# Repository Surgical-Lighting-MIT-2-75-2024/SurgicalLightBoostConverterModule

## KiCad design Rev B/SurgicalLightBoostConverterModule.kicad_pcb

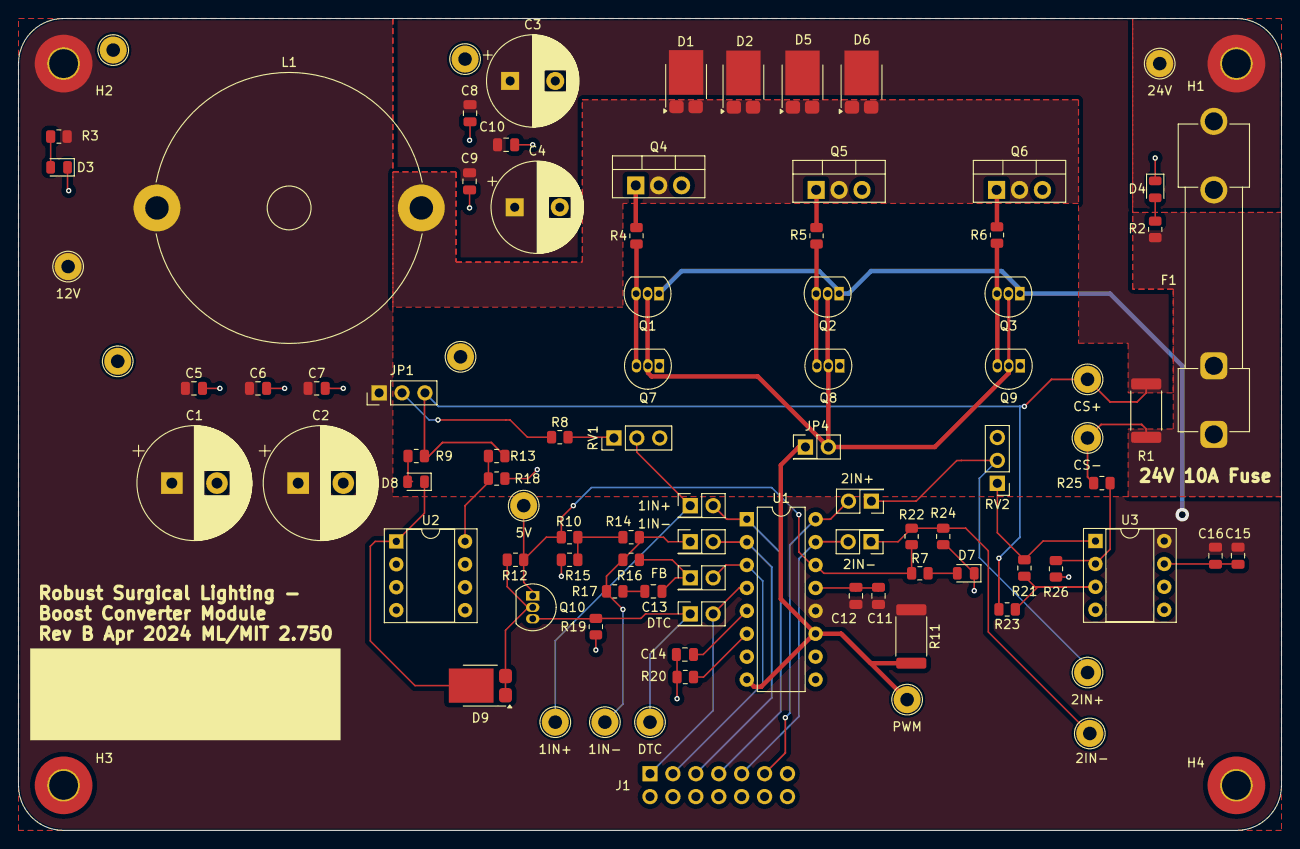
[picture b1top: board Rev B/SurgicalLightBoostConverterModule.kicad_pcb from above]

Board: 2 copper layers, 140.0 x 90.0 mm, 96 parts (1 on the bottom side), 43 nets.

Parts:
1IN+: 1IN+; TestPoint_Loop_D2.54mm_Drill1.5mm_Beaded
1IN+#2: JMPR_1IN+; PinHeader_2x01_P2.54mm_Vertical
1IN-: 1IN-; TestPoint_Loop_D2.54mm_Drill1.5mm_Beaded
1IN-#2: JMPR_1IN-; PinHeader_2x01_P2.54mm_Vertical
2IN+: JMPR_2IN+; PinHeader_2x01_P2.54mm_Vertical
2IN+#2: 2IN+; TestPoint_Loop_D2.54mm_Drill1.5mm_Beaded
2IN-: 2IN-; TestPoint_Loop_D2.54mm_Drill1.5mm_Beaded
2IN-#2: JMPR_2IN-; PinHeader_2x01_P2.54mm_Vertical
5V: 5V; TestPoint_Loop_D2.54mm_Drill1.5mm_Beaded
12V: +12V; TestPoint_Loop_D2.54mm_Drill1.5mm_Beaded
24V: 24V; TestPoint_Loop_D2.54mm_Drill1.5mm_Beaded
C1, C2: 470uF; CP_Radial_D12.5mm_P5.00mm
C3, C4: 220uF; CP_Radial_D10.0mm_P5.00mm
C5, C6, C7, C8, C9, C10, C12, C13, C16: 0.1uF; C_0805_2012Metric
C11, C15: 1uF; C_0805_2012Metric
C14: 1nF; C_0805_2012Metric
CS+: CS+; TestPoint_Loop_D2.54mm_Drill1.5mm_Beaded
CS-: CS-; TestPoint_Loop_D2.54mm_Drill1.5mm_Beaded
D1, D2, D5, D6, D9: PMEG045V150EPD; Nexperia_CFP15_SOT-1289
D3, D4, D7: LED Green; LED_0805_2012Metric
D8: LED Red; LED_0805_2012Metric
DTC: JMPR_DTC; PinHeader_2x01_P2.54mm_Vertical
DTC#2: DTC; TestPoint_Loop_D2.54mm_Drill1.5mm_Beaded
F1: 12A; Fuseholder_Clip-6.3x32mm_Littelfuse_102071_Inline_P34.70x7.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
FB: JMPR_FB; PinHeader_2x01_P2.54mm_Vertical
H1, H2, H3, H4: M3 Hole; MountingHole_3.2mm_M3_Pad_TopBottom
J1: 2x7 P2.54mm; PinHeader_2x07_P2.54mm_Vertical
JP1: JMPR_VFB; PinHeader_1x03_P2.54mm_Vertical
JP4: JMPR_PWM; PinHeader_2x01_P2.54mm_Vertical
L1: 68uH 11.4A; L_Radial_D29.8mm_P29.30mm_Murata_1400series
PWM: PWM; TestPoint_Loop_D2.54mm_Drill1.5mm_Beaded
Q1, Q2, Q3: BC337; TO-92_Inline
Q4, Q5, Q6: AOT240L; TO-220-3_Vertical
Q7, Q8, Q9, Q10: BC327; TO-92_Inline
R1: 5mR; R_2512_6332Metric
R2: 4K7; R_0805_2012Metric
R3, R19: 2K2; R_0805_2012Metric
R4, R5, R6: 10; R_0805_2012Metric
R7: 330; R_0805_2012Metric
R8: 38K; R_0805_2012Metric
R9: 3K3; R_0805_2012Metric
R10, R12, R15, R22, R24: 10K; R_0805_2012Metric
R11: 100; R_2512_6332Metric
R13: 9.1K; R_0805_2012Metric
R14, R18, R23, R25: 1K; R_0805_2012Metric
R16, R21, R26: 100K; R_0805_2012Metric
R17: 82K; R_0805_2012Metric
R20: 3K9; R_0805_2012Metric
RV1, RV2: 10K; PinHeader_1x03_P2.54mm_Vertical
TP1: LMount1; TestPoint_Loop_D2.54mm_Drill1.5mm_Beaded
TP2: LMount2; TestPoint_Loop_D2.54mm_Drill1.5mm_Beaded
TP3: LMount4; TestPoint_Loop_D2.54mm_Drill1.5mm_Beaded
TP4: LMount3; TestPoint_Loop_D2.54mm_Drill1.5mm_Beaded
U1: TL494; DIP-16_W7.62mm
U2: TL431D; DIP-8_W7.62mm_Socket
U3: LM358; DIP-8_W7.62mm_Socket

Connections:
+5V: 5V.1, Q10.1 (C), R7.1, R10.1, R12.1, R22.1, U1.14 (REF)
+12V: 12V.1, C1.1, C2.1, C5.1, C6.1, C7.1, C11.1, C12.1, C15.1, C16.1, H2.1, JP1.1 (A), L1.1, Q1.1 (C), Q2.1 (C), Q3.1 (C), R3.1, R11.1, U1.12 (VCC), U3.8 (V+)
+24V: 24V.1, F1.2, H1.1
/1IN+: 1IN+#2.2 (B), J1.7, U1.1 (1IN+)
/1IN-: 1IN-#2.2 (B), J1.5, U1.2 (1IN-)
/2IN+: 2IN+.2 (B), J1.11, U1.16 (2IN+)
/2IN-: 2IN-#2.2 (B), J1.9, U1.15 (2IN-)
/CS+: C3.1, C4.1, C8.1, C9.1, C10.1, CS+.1, D1.3 (K), D2.3 (K), D5.3 (K), D6.3 (K), JP1.3 (B), R1.1, R9.1, R13.1, R23.2
/CS-: CS-.1, F1.1, R1.2, R2.1, R25.1
/DTC: DTC.2 (B), J1.1, U1.4 (DTC)
/FB: FB.2 (B), J1.3, U1.3 (FB)
/VSwitch: D1.1 (A), D1.2 (A), D2.1 (A), D2.2 (A), D5.1 (A), D5.2 (A), D6.1 (A), D6.2 (A), L1.2, Q4.2 (D), Q5.2 (D), Q6.2 (D)
GND: C1.2, C2.2, C3.2, C4.2, C5.2, C6.2, C7.2, C8.2, C9.2, C10.2, C11.2, C12.2, C14.2, C15.2, C16.2, D3.1 (K), D4.1 (K), D7.1 (K), H3.1, H4.1, J1.14, Q4.3 (S), Q5.3 (S), Q6.3 (S), Q7.1 (C), Q8.1 (C), Q9.1 (C), R15.2, R18.2, R19.2, R20.2, R24.2, R26.1, RV1.3, RV2.3, U1.7 (GND), U1.9 (E1), U1.10 (E2), U1.13 (OUTCTRL), U2.2 (A), U2.3 (A), U2.6 (A), U2.7 (A), U3.4 (V-), U3.5 (+), U3.6 (-), U3.7
unnamed: C13.1, R17.2
unnamed: D3.2 (A), R3.2
unnamed: D4.2 (A), R2.2
unnamed: D7.2 (A), R7.2
unnamed: D8.2 (A), R9.2
unnamed: D8.1 (K), D9.3 (K), U2.1 (K)
unnamed: JP1.2 (C), R8.1
unnamed: 1IN+.1, 1IN+#2.1 (A), RV1.2
unnamed: 1IN-.1, 1IN-#2.1 (A), R14.2, R16.1, R17.1
unnamed: JP4.1 (A), PWM.1, R11.2, U1.8 (C1), U1.11 (C2)
unnamed: C13.2, FB.1 (A), R16.2
unnamed: DTC.1 (A), DTC#2.1, Q10.3 (E), R19.1
unnamed: 2IN-.1, 2IN-#2.1 (A), R22.2, R24.1
unnamed: 2IN+.1 (A), 2IN+#2.1, RV2.2
unnamed: Q1.3 (E), Q7.3 (E), R4.1
unnamed: Q2.3 (E), Q8.3 (E), R5.1
unnamed: Q3.3 (E), Q9.3 (E), R6.1
unnamed: Q4.1 (G), R4.2
unnamed: Q5.1 (G), R5.2
unnamed: Q6.1 (G), R6.2
unnamed: D9.1 (A), D9.2 (A), Q10.2 (B), R12.2
unnamed: R8.2, RV1.1
unnamed: R10.2, R14.1, R15.1
unnamed: R21.1, RV2.1, U3.1
unnamed: C14.1, U1.5 (CT)
unnamed: R20.1, U1.6 (RT)
unnamed: R13.2, R18.1, U2.8 (REF)
unnamed: R21.2, R23.1, U3.3 (+)
unnamed: R25.2, R26.2, U3.2 (-)
PWM: JP4.2 (B), Q1.2 (B), Q2.2 (B), Q3.2 (B), Q7.2 (B), Q8.2 (B), Q9.2 (B)

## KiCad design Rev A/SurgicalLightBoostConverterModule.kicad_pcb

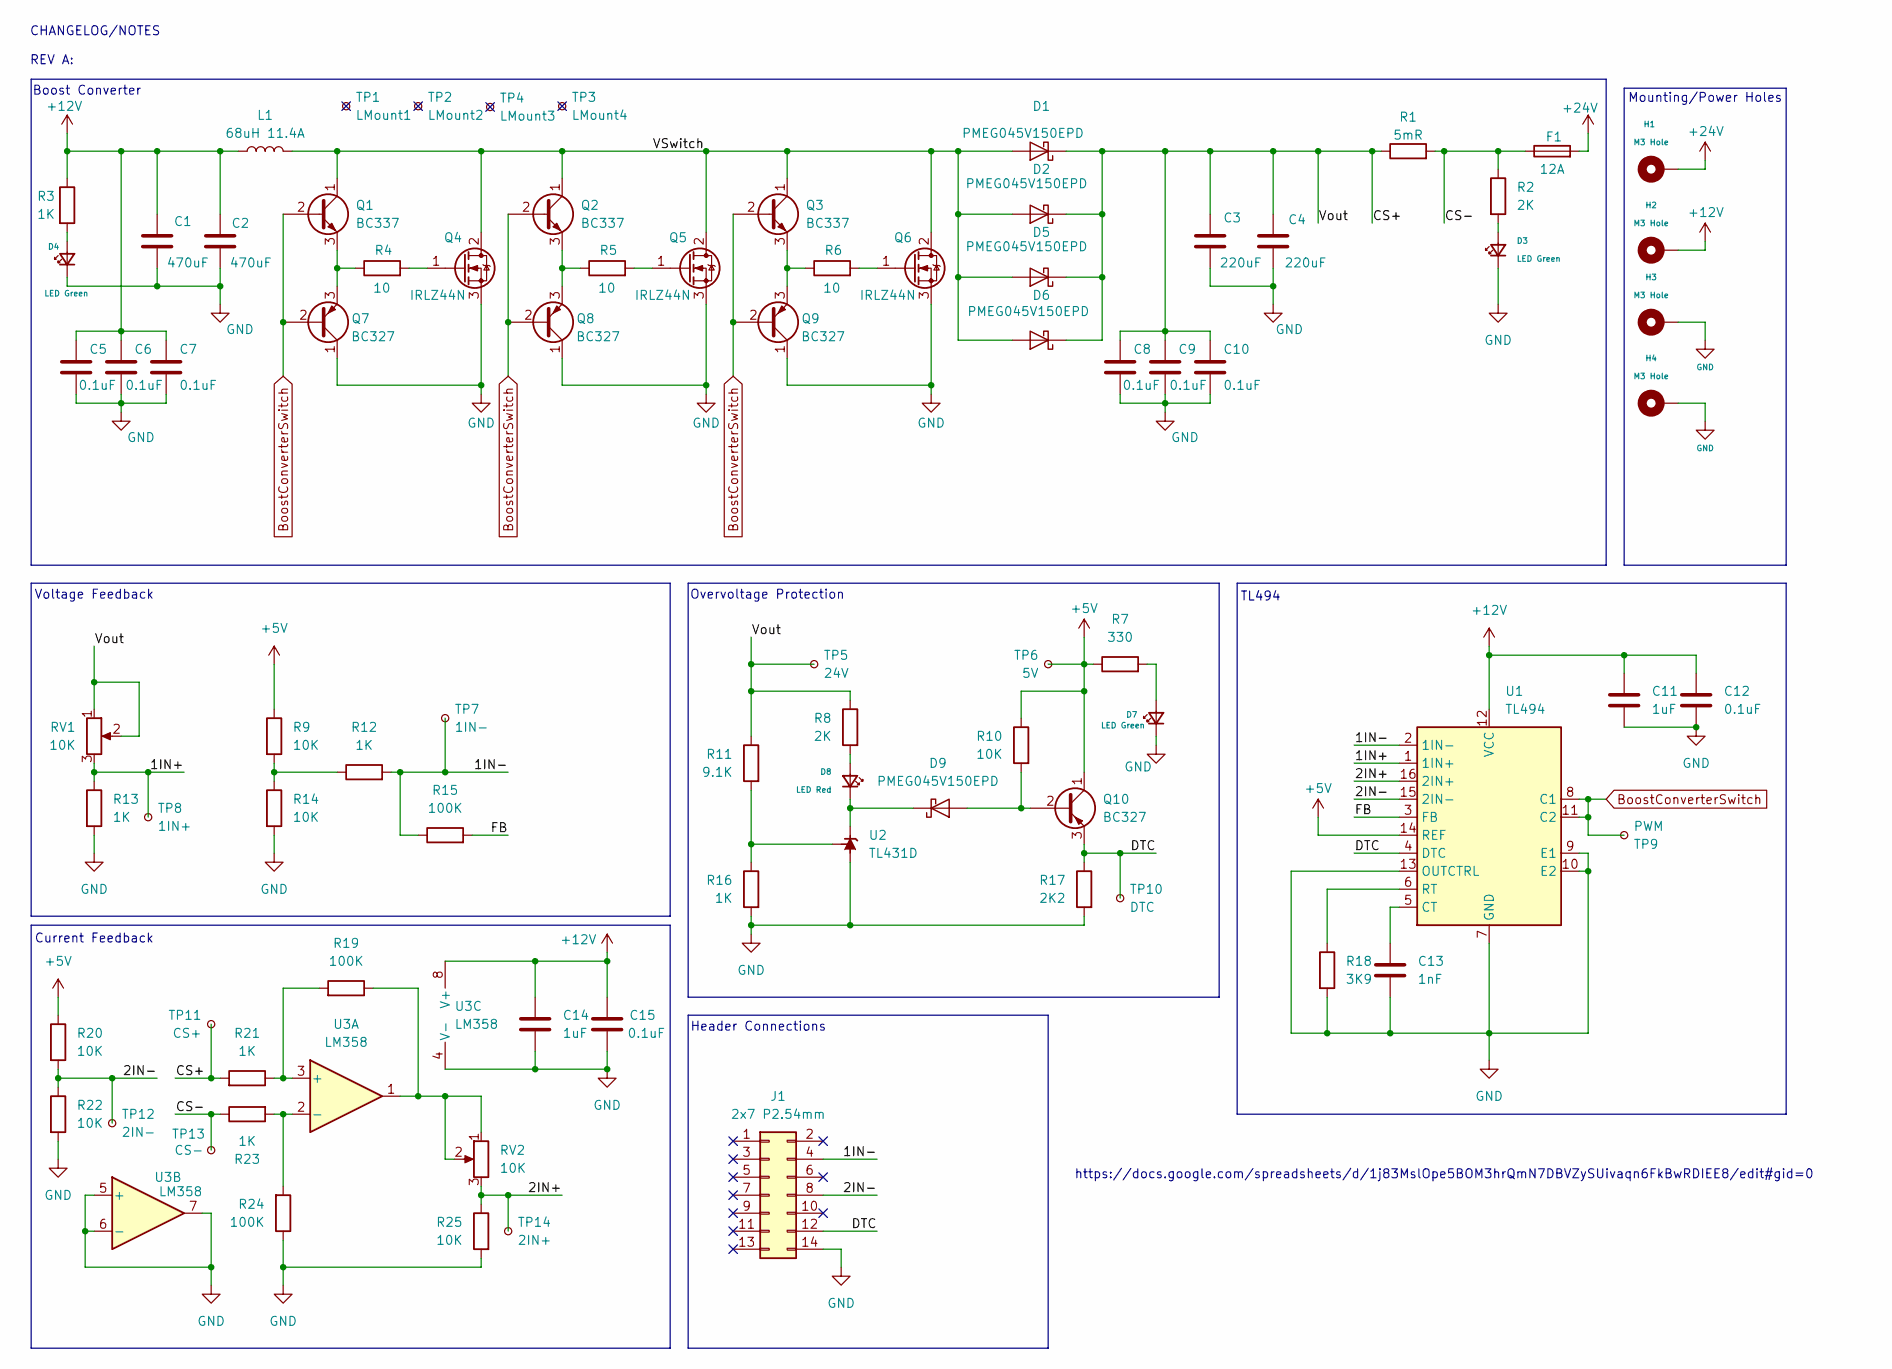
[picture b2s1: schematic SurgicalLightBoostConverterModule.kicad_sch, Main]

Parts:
C1, C2: 470uF; CP_Radial_D12.5mm_P5.00mm
C3, C4: 220uF; CP_Radial_D10.0mm_P5.00mm
C5, C6, C7, C8, C9, C10, C12, C15: 0.1uF; C_0805_2012Metric
C11, C14: 1uF; C_0805_2012Metric
C13: 1nF; C_0805_2012Metric
D1, D2, D5, D6, D9: PMEG045V150EPD; Nexperia_CFP15_SOT-1289
D3, D4, D7: LED Green; LED_0805_2012Metric
D8: LED Red; LED_0805_2012Metric
F1: 12A; Fuseholder_Clip-6.3x32mm_Littelfuse_102071_Inline_P34.70x7.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
H1, H2, H3, H4: M3 Hole; MountingHole_3.2mm_M3_Pad_TopBottom
J1: 2x7 P2.54mm; PinHeader_2x07_P2.54mm_Vertical
L1: 68uH 11.4A; L_Radial_D29.8mm_P29.30mm_Murata_1400series
Q1, Q2, Q3: BC337; TO-92_Inline
Q4, Q5, Q6: IRLZ44N; TO-220-3_Vertical
Q7, Q8, Q9, Q10: BC327; TO-92_Inline
R1: 5mR; R_2512_6332Metric
R2, R8: 2K; R_0805_2012Metric
R3, R12, R13, R16, R21, R23: 1K; R_0805_2012Metric
R4, R5, R6: 10; R_0805_2012Metric
R7: 330; R_0805_2012Metric
R9, R10, R14, R20, R22, R25: 10K; R_0805_2012Metric
R11: 9.1K; R_0805_2012Metric
R15, R19, R24: 100K; R_0805_2012Metric
R17: 2K2; R_0805_2012Metric
R18: 3K9; R_0805_2012Metric
RV1, RV2: 10K; PinHeader_1x03_P2.54mm_Vertical
TP1: LMount1; TestPoint_Loop_D2.54mm_Drill1.5mm_Beaded
TP2: LMount2; TestPoint_Loop_D2.54mm_Drill1.5mm_Beaded
TP3: LMount4; TestPoint_Loop_D2.54mm_Drill1.5mm_Beaded
TP4: LMount3; TestPoint_Loop_D2.54mm_Drill1.5mm_Beaded
TP5: 24V; TestPoint_Loop_D2.54mm_Drill1.5mm_Beaded
TP6: 5V; TestPoint_Loop_D2.54mm_Drill1.5mm_Beaded
TP7: 1IN-; TestPoint_Loop_D2.54mm_Drill1.5mm_Beaded
TP8: 1IN+; TestPoint_Loop_D2.54mm_Drill1.5mm_Beaded
TP9: PWM; TestPoint_Loop_D2.54mm_Drill1.5mm_Beaded
TP10: DTC; TestPoint_Loop_D2.54mm_Drill1.5mm_Beaded
TP11: CS+; TestPoint_Loop_D2.54mm_Drill1.5mm_Beaded
TP12: 2IN-; TestPoint_Loop_D2.54mm_Drill1.5mm_Beaded
TP13: CS-; TestPoint_Loop_D2.54mm_Drill1.5mm_Beaded
TP14: 2IN+; TestPoint_Loop_D2.54mm_Drill1.5mm_Beaded
U1: TL494; DIP-16_W7.62mm
U2: TL431D; DIP-8_W7.62mm_Socket
U3: LM358; DIP-8_W7.62mm_Socket

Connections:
+5V: Q10.1 (C), R7.1, R9.1, R10.1, R20.1, TP6.1, U1.14 (REF)
+12V: C1.1, C2.1, C5.1, C6.1, C7.1, C11.1, C12.1, C14.1, C15.1, H2.1, L1.1, R3.1, U1.12 (VCC), U3.8 (V+)
+24V: F1.2, H1.1
/1IN+: R13.1, RV1.3, TP8.1, U1.1 (1IN+)
/1IN-: J1.4, R12.2, R15.1, TP7.1, U1.2 (1IN-)
/2IN+: R25.1, RV2.3, TP14.1, U1.16 (2IN+)
/2IN-: J1.8, R20.2, R22.1, TP12.1, U1.15 (2IN-)
/CS+: C3.1, C4.1, C8.1, C9.1, C10.1, D1.3 (K), D2.3 (K), D5.3 (K), D6.3 (K), R1.1, R8.1, R11.1, R21.2, RV1.1, RV1.2, TP5.1, TP11.1
/CS-: F1.1, R1.2, R2.1, R23.1, TP13.1
/DTC: J1.12, Q10.3 (E), R17.1, TP10.1, U1.4 (DTC)
/FB: R15.2, U1.3 (FB)
/VSwitch: D1.1 (A), D1.2 (A), D2.1 (A), D2.2 (A), D5.1 (A), D5.2 (A), D6.1 (A), D6.2 (A), L1.2, Q1.1 (C), Q2.1 (C), Q3.1 (C), Q4.2 (D), Q5.2 (D), Q6.2 (D)
BoostConverterSwitch: Q1.2 (B), Q2.2 (B), Q3.2 (B), Q7.2 (B), Q8.2 (B), Q9.2 (B), TP9.1, U1.8 (C1), U1.11 (C2)
GND: C1.2, C2.2, C3.2, C4.2, C5.2, C6.2, C7.2, C8.2, C9.2, C10.2, C11.2, C12.2, C13.2, C14.2, C15.2, D3.1 (K), D4.1 (K), D7.1 (K), H3.1, H4.1, J1.14, Q4.3 (S), Q5.3 (S), Q6.3 (S), Q7.1 (C), Q8.1 (C), Q9.1 (C), R13.2, R14.2, R16.2, R17.2, R18.2, R22.2, R24.1, R25.2, U1.7 (GND), U1.9 (E1), U1.10 (E2), U1.13 (OUTCTRL), U2.2 (A), U2.3 (A), U2.6 (A), U2.7 (A), U3.4 (V-), U3.5 (+), U3.6 (-), U3.7
unnamed: D3.2 (A), R2.2
unnamed: D4.2 (A), R3.2
unnamed: D7.2 (A), R7.2
unnamed: D8.2 (A), R8.2
unnamed: D8.1 (K), D9.3 (K), U2.1 (K)
unnamed: Q1.3 (E), Q7.3 (E), R4.1
unnamed: Q2.3 (E), Q8.3 (E), R5.1
unnamed: Q3.3 (E), Q9.3 (E), R6.1
unnamed: Q4.1 (G), R4.2
unnamed: Q5.1 (G), R5.2
unnamed: Q6.1 (G), R6.2
unnamed: D9.1 (A), D9.2 (A), Q10.2 (B), R10.2
unnamed: R9.2, R12.1, R14.1
unnamed: R19.1, RV2.1, RV2.2, U3.1
unnamed: C13.1, U1.5 (CT)
unnamed: R18.1, U1.6 (RT)
unnamed: R11.2, R16.1, U2.8 (REF)
unnamed: R19.2, R21.1, U3.3 (+)
unnamed: R23.2, R24.2, U3.2 (-)

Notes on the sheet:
TL494
Boost Converter
https://docs.google.com/spreadsheets/d/1j83MslOpe5BOM3hrQmN7DBVZySUivaqn6FkBwRDIEE8/edit#gid=0
Voltage Feedback
Mounting/Power Holes
Overvoltage Protection
Current Feedback
Header Connections
CHANGELOG/NOTES REV A:

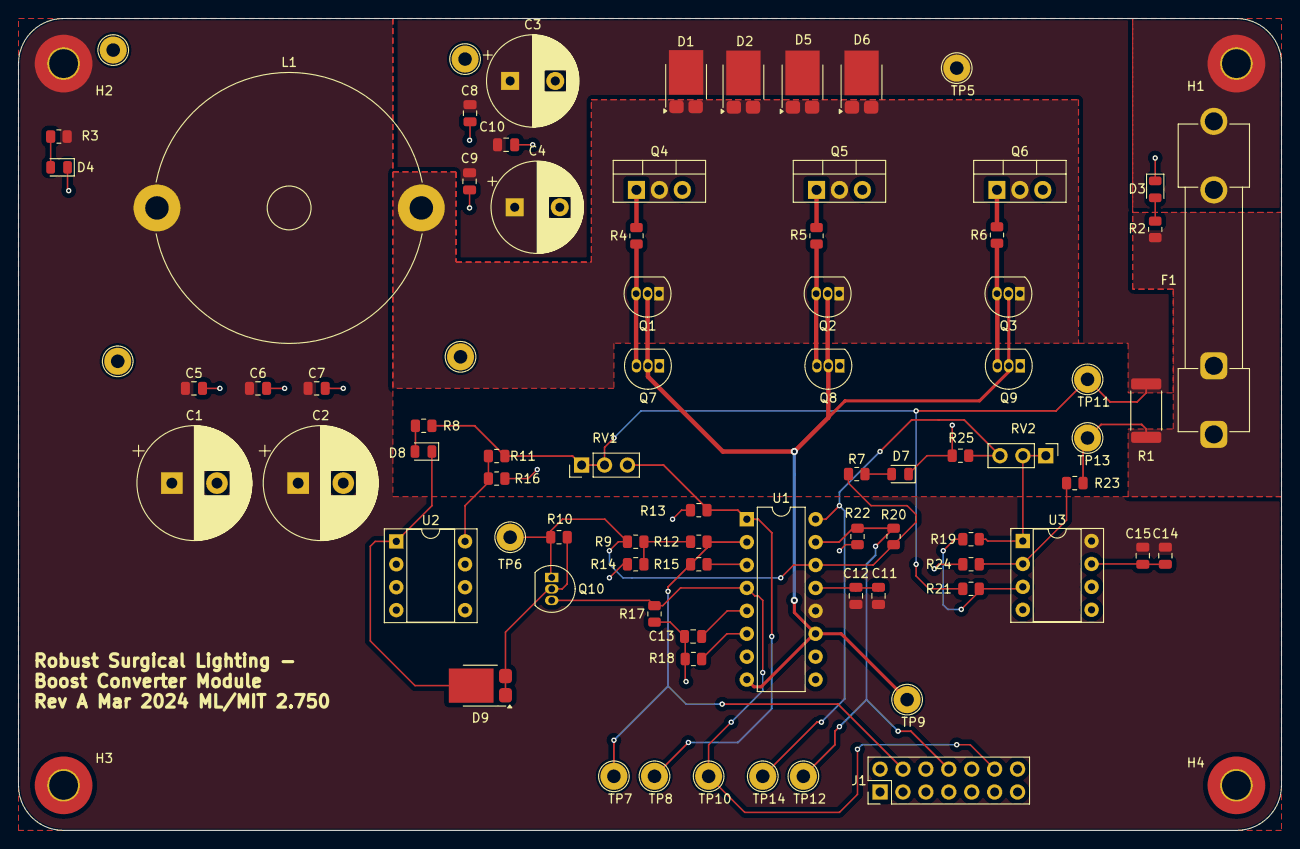
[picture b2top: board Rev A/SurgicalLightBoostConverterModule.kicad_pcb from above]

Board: 2 copper layers, 140.0 x 90.0 mm, 85 parts (0 on the bottom side), 33 nets.

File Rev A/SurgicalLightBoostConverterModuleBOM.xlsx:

Id | Designator | Footprint | Quantity | Designation | Supplier and ref
1 | R15,R24,R19 | R_0805_2012Metric | 3 | 100K | RMCF0805FT100KCT-ND
2 | R16,R21,R3,R13,R12,R23 | R_0805_2012Metric | 6 | 1K | RMCF0805FT1K00CT-ND
3 | R9,R22,R25,R20,R10,R14 | R_0805_2012Metric | 6 | 10K | RMCF0805FT10K0CT-ND
4 | U1 | DIP-16_W7.62mm | 1 | TL494 | 296-10194-5-ND
5 | Q1,Q2,Q3 | TO-92_Inline | 3 | BC337 | BC337-25-APMSCT-ND
6 | TP6 | TestPoint_Loop_D2.54mm_Drill1.5mm_Beaded | 1 | 5V | 36-5260-ND
7 | R4,R5,R6 | R_0805_2012Metric | 3 | 10 | RMCF0805FT10R0CT-ND
8 | R8,R2 | R_0805_2012Metric | 2 | 2K | RNCP0805FTD2K00CT-ND
9 | C1,C2 | CP_Radial_D12.5mm_P5.00mm | 2 | 470uF | 1189-2329-ND
10 | TP13 | TestPoint_Loop_D2.54mm_Drill1.5mm_Beaded | 1 | CS- | 36-5264-ND
11 | C12,C7,C5,C6,C8,C10,C15,C9 | C_0805_2012Metric | 8 | 0.1uF | 1276-1003-1-ND
12 | R7 | R_0805_2012Metric | 1 | 330 | RMCF0805FT330RCT-ND
13 | C13 | C_0805_2012Metric | 1 | 1nF | 1276-1091-1-ND
14 | Q9,Q10,Q7,Q8 | TO-92_Inline | 4 | BC327 | BC32725BUFS-ND
15 | D3,D7,D4 | LED_0805_2012Metric | 3 | LED Green | 732-4983-1-ND
16 | J1 | PinHeader_2x07_P2.54mm_Vertical | 1 | 2x7 P2.54mm | 2057-PH2-14-UA-ND
17 | C11,C14 | C_0805_2012Metric | 2 | 1uF | 1276-1029-1-ND
18 | D5,D9,D2,D1,D6 | Nexperia_CFP15_SOT-1289 | 5 | PMEG045V150EPD | 1727-7635-1-ND
19 | L1 | L_Radial_D29.8mm_P29.30mm_Murata_1400series | 1 | 68uH 11.4A | M8376-ND
20 | Q4,Q5,Q6 | TO-220-3_Vertical | 3 | IRLZ44N | IRLZ44NPBF | or IRFZ44NPBF idk whatever ur getting dude
21 | TP1 | TestPoint_Loop_D2.54mm_Drill1.5mm_Beaded | 1 | LMount1 | N/A
22 | R17 | R_0805_2012Metric | 1 | 2K2 | RMCF0805FT2K20CT-ND
23 | U2 | DIP-8_W7.62mm_Socket | 1 | TL431D | 296-10182-5-ND
24 | TP12 | TestPoint_Loop_D2.54mm_Drill1.5mm_Beaded | 1 | 2IN- | 36-5269-ND
25 | TP8 | TestPoint_Loop_D2.54mm_Drill1.5mm_Beaded | 1 | 1IN+ | 36-5269-ND
26 | TP3 | TestPoint_Loop_D2.54mm_Drill1.5mm_Beaded | 1 | LMount4 | N/A
27 | C4,C3 | CP_Radial_D10.0mm_P5.00mm | 2 | 220uF | 1189-1759-ND
28 | TP2 | TestPoint_Loop_D2.54mm_Drill1.5mm_Beaded | 1 | LMount2 | N/A
29 | TP4 | TestPoint_Loop_D2.54mm_Drill1.5mm_Beaded | 1 | LMount3 | N/A
30 | D8 | LED_0805_2012Metric | 1 | LED Red | 732-4984-1-ND
31 | R11 | R_0805_2012Metric | 1 | 9.1K | 738-RMCF0805FT9K10CT-ND
32 | F1 | Fuseholder_Clip-6.3x32mm_Littelfuse_102071_Inline_P34.70x7.60mm_D2.00mm_Horizon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 | 1 | 12A | 507-2231-ND
33 | R1 | R_2512_6332Metric | 1 | 5mR | CRF2512-FZ-R005ELFCT-ND
34 | TP5 | TestPoint_Loop_D2.54mm_Drill1.5mm_Beaded | 1 | 24V | 36-5260-ND
35 | TP10 | TestPoint_Loop_D2.54mm_Drill1.5mm_Beaded | 1 | DTC | 36-5269-ND
36 | TP7 | TestPoint_Loop_D2.54mm_Drill1.5mm_Beaded | 1 | 1IN- | 36-5269-ND
37 | TP11 | TestPoint_Loop_D2.54mm_Drill1.5mm_Beaded | 1 | CS+ | 36-5264-ND
38 | TP14 | TestPoint_Loop_D2.54mm_Drill1.5mm_Beaded | 1 | 2IN+ | 36-5269-ND
39 | U3 | DIP-8_W7.62mm_Socket | 1 | LM358 | 296-1395-5-ND
40 | TP9 | TestPoint_Loop_D2.54mm_Drill1.5mm_Beaded | 1 | PWM | 36-5269-ND
41 | R18 | R_0805_2012Metric | 1 | 3K9 | RMCF0805FT3K90CT-ND
42 | RV2,RV1 | PinHeader_1x03_P2.54mm_Vertical | 2 | 10K | 118-PV36W103C01B00-ND

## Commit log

2024-03-30 First commit.
2024-03-30 Added boost converter.
2024-03-31 Added feedback and protection circuits.
2024-03-31 More schematic updates.
2024-04-01 PCB? :(
2024-04-03 Full layout.
2024-04-04 added michael's changes
2024-04-05 Updated some datasheets.
2024-04-05 Gerber.
2024-04-05 BOM.
2024-04-25 Rev B!
2024-04-26 Silk screen.
2024-04-26 Silk screenz.
2024-04-26 Updated text for testpoints and jumpers.
